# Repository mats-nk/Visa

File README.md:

# "Visa" Introduction

Visa is old norse for "Show" and thats what this project is about.

## First boot:
 - Activate a AP "LED_MATRIX"
 - Configure WiFi and an MQTT broker

## Second boot and thereafter:
 - Publish to MQTT broker what IP it has got
 - Other configuration is acomplished by publish to specific MQTT topics.

# `tools` folder

Here you can find some python tool for get "weather data to MQTT topics" and "MQTT topics to other MQTT topics" with transformation.

### `weather_mqtt.py` — fetches weather from Open-Meteo or wttr.in and publishes to MQTT
 - Multi-language weather descriptions (10 languages)
 - Configurable fields, units, wind direction format
 - In-place countdown between fetches
 - Script version published as MQTT topic

### `mqtt_bridge.py` — forwards MQTT topics with transforms
 - Normal 1-to-1 forwarding
 - Automatic round-robin when multiple sources share the same destination
 - Transform pipeline: round, scale, offset, suffix, prefix, template, json_field
 - Wildcard subscriptions with dynamic destination topics
 - Script version published as MQTT topic

### `setup.sh` — creates the venv, installs dependencies and runs a smoke test

# MQTT Topic Reference

All topics use the pattern `<hostname>/<suffix>`.

Default hostname is `LED_MATRIX`. Replace with your configured hostname throughout.

All values are persisted to EEPROM unless noted otherwise.

---

## Runtime topics

### `LED_MATRIX/value`
Display a message.
- Long messages (wider than display) scroll continuously.
- Short messages (fits on display) are shown statically.
- A queued message waits until the current scroll pass completes before displaying.
- Supports Swedish characters: `å ä ö Å Ä Ö`
- Supports degree symbol: `°` (UTF-8 `0xC2 0xB0`, auto-transcoded to Latin-1 `0xB0`)

```bash
# Plain text
mosquitto_pub -h <MQTT broker> -t "LED_MATRIX/value" -m "Hello World"

# Swedish characters
mosquitto_pub -h <MQTT broker> -t "LED_MATRIX/value" -m "Hej Sverige åäö"

# Temperature with degree symbol
mosquitto_pub -h <MQTT broker> -t "LED_MATRIX/value" -m "Temp: 22°C"
mosquitto_pub -h <MQTT broker> -t "LED_MATRIX/value" -m "Ute: -5°C  Inne: 21°C"

# Time and date (shell substitution)
mosquitto_pub -h <MQTT broker> -t "LED_MATRIX/value" -m "$(date +'%H:%M')"
mosquitto_pub -h <MQTT broker> -t "LED_MATRIX/value" -m "$(date +'%A %d %B')"

# Combined sensor readout
mosquitto_pub -h <MQTT broker> -t "LED_MATRIX/value" -m "$(date +'%H:%M')  Temp: 22°C  Luftfukt: 45%"

# Clear the display
mosquitto_pub -h <MQTT broker> -t "LED_MATRIX/value" -m ""
```

---

### `LED_MATRIX/speed`
Scroll step delay in milliseconds. Lower = faster scroll.

Range: `10` – `500` ms. Default: `100`

```bash
mosquitto_pub -h <MQTT broker> -t "LED_MATRIX/speed" -m "50"    # fast
mosquitto_pub -h <MQTT broker> -t "LED_MATRIX/speed" -m "100"   # default
mosquitto_pub -h <MQTT broker> -t "LED_MATRIX/speed" -m "200"   # slow
```

---

### `LED_MATRIX/intensity`
Display brightness.
Range: `0` (minimum) – `15` (maximum). Default: `5`

```bash
mosquitto_pub -h <MQTT broker> -t "LED_MATRIX/intensity" -m "0"    # minimum (nearly off)
mosquitto_pub -h <MQTT broker> -t "LED_MATRIX/intensity" -m "5"    # default
mosquitto_pub -h <MQTT broker> -t "LED_MATRIX/intensity" -m "15"   # maximum
```

---

### `LED_MATRIX/state`
Turn display on or off.

`1` = on, `0` = off. Not persisted — resets to on after reboot.

When turned back on the previous message resumes automatically.

```bash
mosquitto_pub -h <MQTT broker> -t "LED_MATRIX/state" -m "0"   # off
mosquitto_pub -h <MQTT broker> -t "LED_MATRIX/state" -m "1"   # on
```

---

### `LED_MATRIX/anim`
Animation mode for scrolling messages.

Default: `0`

| Value | Name         | Description                                    |
|-------|------        |-------------                                   |
| `0`   | Scroll left  | Text enters from right, exits left *(default)* |
| `1`   | Scroll right | Text enters from left, exits right             |
| `2`   | Scroll up    | Text shifts upward each tick                   |
| `3`   | Scroll down  | Text shifts downward each tick                 |
| `4`   | Flip LR      | Static left↔right mirror, redrawn each tick    |
| `5`   | Flip UD      | Static top↔bottom mirror, redrawn each tick    |
| `6`   | Rotate CW    | 90° clockwise rotation applied each tick       |
| `7`   | Invert       | All pixels toggled each tick                   |
| `8`   | Bounce       | Ping-pong: scroll left then right alternating  |
| `9`   | Scroll left + invert | Scroll left with inverted pixels       |
| `10`  | Blink        | Whole display blinks at scroll speed           |
| `11`  | Wipe in      | Columns fill inward from both edges            |
| `12`  | Wipe out     | Columns clear outward from centre              |

```bash
mosquitto_pub -h <MQTT broker> -t "LED_MATRIX/anim" -m "0"    # scroll left (default)
mosquitto_pub -h <MQTT broker> -t "LED_MATRIX/anim" -m "1"    # scroll right
mosquitto_pub -h <MQTT broker> -t "LED_MATRIX/anim" -m "8"    # bounce
mosquitto_pub -h <MQTT broker> -t "LED_MATRIX/anim" -m "10"   # blink
```

---

### `LED_MATRIX/pause`
Hold time in milliseconds after each full message pass before restarting.

`0` = no pause (continuous). Max: `30000` ms. Default: `0`

Behaviour differs by message length:
- **Long message (scrolling):** display is blank during the pause.
- **Short message (static):** message stays visible during the pause, then clears briefly before redisplaying.

```bash
mosquitto_pub -h <MQTT broker> -t "LED_MATRIX/pause" -m "0"      # continuous (default)
mosquitto_pub -h <MQTT broker> -t "LED_MATRIX/pause" -m "2000"   # 2 second pause
mosquitto_pub -h <MQTT broker> -t "LED_MATRIX/pause" -m "5000"   # 5 second pause
mosquitto_pub -h <MQTT broker> -t "LED_MATRIX/pause" -m "10000"  # 10 second pause
```

---

### `LED_MATRIX/align`
Text alignment for short messages that fit within the display width.

Has no effect on scrolling messages. Default: `0`

| Value | Alignment |
|-------|-----------|
| `0` | Left *(default)* |
| `1` | Centre |
| `2` | Right |

```bash
mosquitto_pub -h <MQTT broker> -t "LED_MATRIX/align" -m "0"   # left (default)
mosquitto_pub -h <MQTT broker> -t "LED_MATRIX/align" -m "1"   # centre — good for time "12:45"
mosquitto_pub -h <MQTT broker> -t "LED_MATRIX/align" -m "2"   # right
```

---

## Hardware config topics

Changes to hardware config topics trigger a full matrix reinitialisation without reboot.

The display briefly shows `reconfigured!` then resumes the previous message.

### `LED_MATRIX/config/hwtype`
MAX7219 module hardware type.

Default: `3` (FC16)

| Value | Type |
|-------|------|
| `0` | PAROLA_HW |
| `1` | GENERIC_HW |
| `2` | ICSTATION_HW |
| `3` | FC16_HW *(default)* |

```bash
mosquitto_pub -h <MQTT broker> -t "LED_MATRIX/config/hwtype" -m "3"   # FC16 (most common)
mosquitto_pub -h <MQTT broker> -t "LED_MATRIX/config/hwtype" -m "1"   # Generic
```

---

### `LED_MATRIX/config/numdevices`
Number of chained MAX7219 modules.

Range: `1` – `8`. Default: `4`

```bash
mosquitto_pub -h <MQTT broker> -t "LED_MATRIX/config/numdevices" -m "4"   # 4 modules
mosquitto_pub -h <MQTT broker> -t "LED_MATRIX/config/numdevices" -m "8"   # 8 modules
```

---

### `LED_MATRIX/config/clkpin`
GPIO number for SPI CLK.

Default (ESP8266 D1 Mini): `14` (D5)

```bash
mosquitto_pub -h <MQTT broker> -t "LED_MATRIX/config/clkpin" -m "14"
```

---

### `LED_MATRIX/config/datapin`
GPIO number for SPI DATA/MOSI.

Default (ESP8266 D1 Mini): `13` (D7)

```bash
mosquitto_pub -h <MQTT broker> -t "LED_MATRIX/config/datapin" -m "13"
```

---

### `LED_MATRIX/config/cspin`
GPIO number for SPI CS/SS.

Default (ESP8266 D1 Mini): `12` (D6)

```bash
mosquitto_pub -h <MQTT broker> -t "LED_MATRIX/config/cspin" -m "12"
```

---

### `LED_MATRIX/config/auxpin`
GPIO number for auxiliary output (e.g. LDR enable).

Default (ESP8266): `3`

```bash
mosquitto_pub -h <MQTT broker> -t "LED_MATRIX/config/auxpin" -m "3"
```

---

### `LED_MATRIX/config/hbledpin`
GPIO number for heartbeat LED.

Default (ESP8266): `2`

```bash
mosquitto_pub -h <MQTT broker> -t "LED_MATRIX/config/hbledpin" -m "2"
```

---

### `matrix/config/hostname`
Rename the device. **Fixed topic** — always `matrix/config/hostname` regardless of current hostname, so any device can be targeted before its hostname is known.

Max 31 characters. Takes effect immediately — device reconnects to MQTT with the new name.

```bash
mosquitto_pub -h <MQTT broker> -t "matrix/config/hostname" -m "LOBBY"
mosquitto_pub -h <MQTT broker> -t "matrix/config/hostname" -m "RECEPTION"
mosquitto_pub -h <MQTT broker> -t "matrix/config/hostname" -m "LED_MATRIX"   # reset to default
```

---

## Status topic (published by device)

### `LED_MATRIX/config/status`
Published by the device on every MQTT connect and after errors.
Includes firmware version as the first field.

```
fw=2025-03-07.1 hostname=LED_MATRIX mqtt=<MQTT broker>:1883 hwType=3 devices=8 clk=14 data=13 cs=12 aux=3 hbled=2 speed=100 intensity=5 anim=0 pause=0 align=0
```

```bash
# Subscribe to watch status
mosquitto_sub -h <MQTT broker> -t "LED_MATRIX/config/status"

# Trigger a status republish by cycling state
mosquitto_pub -h <MQTT broker> -t "LED_MATRIX/state" -m "1"
```

---

## Active/online topic (published by device)

### `LED_MATRIX/active`
Published as `online` on every MQTT connect. Used by Home Assistant as the availability topic — entities show as unavailable if the device drops off the network.

```bash
mosquitto_sub -h <MQTT broker> -t "LED_MATRIX/active"
```

---

## Practical examples

### Clock display — centred, refreshed every minute
```bash
# Set up display style once
mosquitto_pub -h <MQTT broker> -t "LED_MATRIX/align"   -m "1"     # centre
mosquitto_pub -h <MQTT broker> -t "LED_MATRIX/pause"   -m "0"     # no pause
mosquitto_pub -h <MQTT broker> -t "LED_MATRIX/anim"    -m "0"

# Then update time each minute via cron or Home Assistant automation
mosquitto_pub -h <MQTT broker> -t "LED_MATRIX/value"   -m "$(date +'%H:%M')"
```

### Temperature ticker from Home Assistant
```bash
# Long scrolling message with temperature and humidity
mosquitto_pub -h <MQTT broker> -t "LED_MATRIX/value" -m "Ute: -3°C  Inne: 21°C  Luftfukt: 42%"
mosquitto_pub -h <MQTT broker> -t "LED_MATRIX/speed" -m "80"
mosquitto_pub -h <MQTT broker> -t "LED_MATRIX/pause" -m "3000"
```

### Night mode — dim and slow
```bash
mosquitto_pub -h <MQTT broker> -t "LED_MATRIX/intensity" -m "1"
mosquitto_pub -h <MQTT broker> -t "LED_MATRIX/speed"     -m "150"
```

### Day mode — bright and fast
```bash
mosquitto_pub -h <MQTT broker> -t "LED_MATRIX/intensity" -m "10"
mosquitto_pub -h <MQTT broker> -t "LED_MATRIX/speed"     -m "60"
```

### Turn off at bedtime, on at wake-up
```bash
mosquitto_pub -h <MQTT broker> -t "LED_MATRIX/state" -m "0"   # off — previous message saved
mosquitto_pub -h <MQTT broker> -t "LED_MATRIX/state" -m "1"   # on  — previous message resumes
```

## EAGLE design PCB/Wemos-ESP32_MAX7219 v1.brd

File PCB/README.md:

# MAX7219 4x8x8 matrix module

# ESP8266 

# ESP32

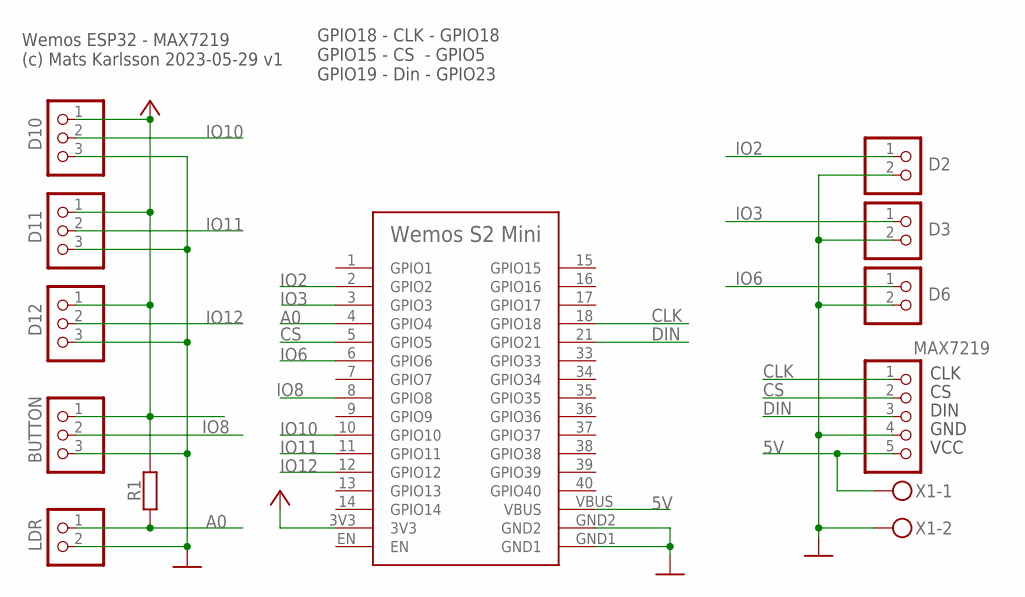
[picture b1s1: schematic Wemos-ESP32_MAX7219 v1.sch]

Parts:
BUTTON: PINHD-1X3; 1X03
D2, D3, D6: PINHD-1X2; 1X02
D10, D11, D12: PINHD-1X3; 1X03
LDR: PINHD-1X2; 1X02
MAX7219: PINHD-1X5; 1X05
R1: R-EU_M0805; M0805
U$1: WEMOS_S2_MINI
X1: W237-102

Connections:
5V: MAX7219.5, U$1.VBUS, X1.1
A0: LDR.1, R1.2, U$1.4 (GPIO4)
CLK: MAX7219.1, U$1.18 (GPIO18)
CS: MAX7219.2, U$1.5 (GPIO5)
DIN: MAX7219.3, U$1.21 (GPIO21)
GND: BUTTON.3, D2.2, D3.2, D6.2, D10.3, D11.3, D12.3, LDR.2, MAX7219.4, U$1.GND1, U$1.GND2, X1.2
IO2: D2.1, U$1.2 (GPIO2)
IO3: D3.1, U$1.3 (GPIO3)
IO6: D6.1, U$1.6 (GPIO6)
IO8: BUTTON.2, U$1.8 (GPIO8)
IO10: D10.2, U$1.10 (GPIO10)
IO11: D11.2, U$1.11 (GPIO11)
IO12: D12.2, U$1.12 (GPIO12)
VCC: BUTTON.1, D10.1, D11.1, D12.1, R1.1, U$1.3V3

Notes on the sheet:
Wemos ESP32 - MAX7219 (c) Mats Karlsson 2023-05-29 v1
GPIO18 - CLK - GPIO18 GPIO15 - CS - GPIO5 GPIO19 - Din - GPIO23
CLK
DIN
GND
VCC

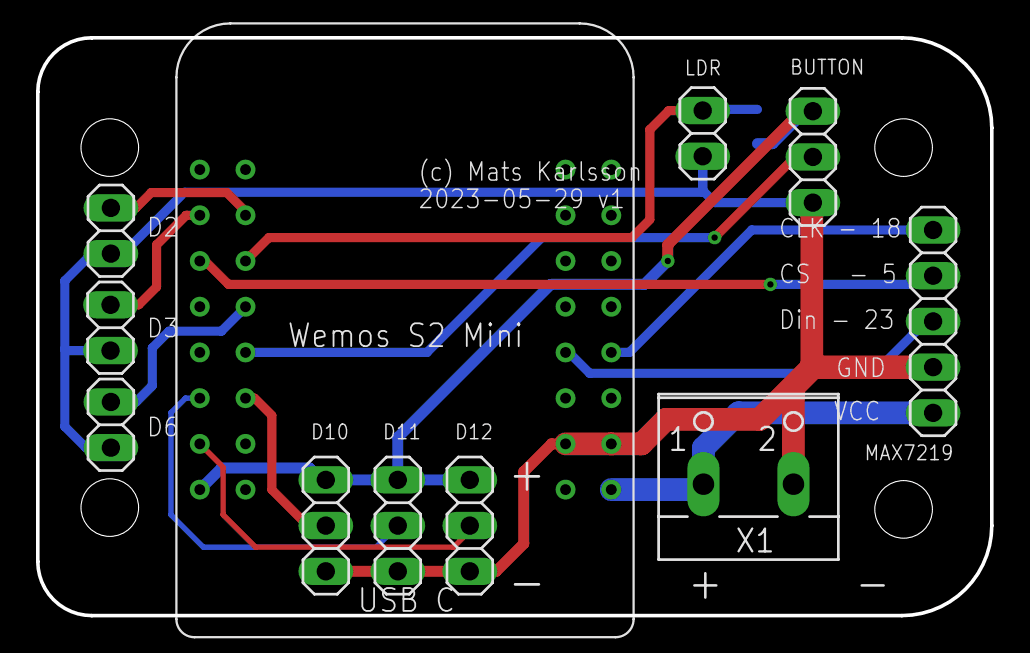
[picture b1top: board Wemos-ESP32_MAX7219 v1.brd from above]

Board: 2 copper layers, 53.0 x 32.1 mm, 12 parts (1 on the bottom side), 14 nets.

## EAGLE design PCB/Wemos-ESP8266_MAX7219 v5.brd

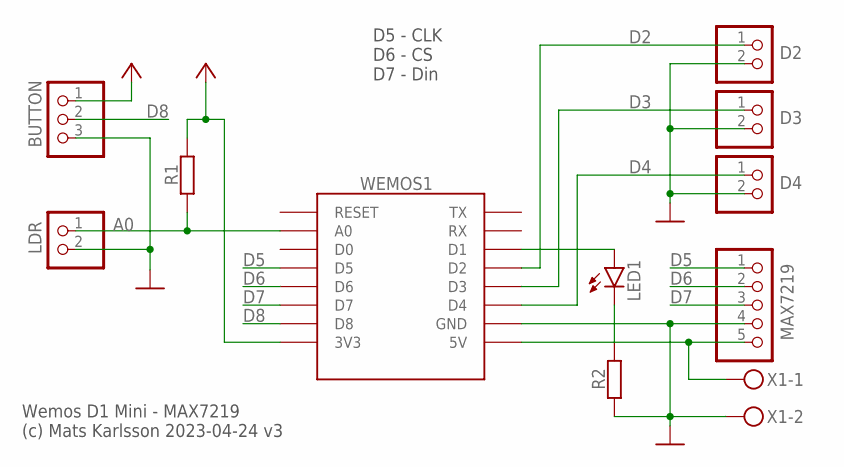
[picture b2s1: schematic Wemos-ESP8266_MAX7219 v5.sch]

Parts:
BUTTON: PINHD-1X3; 1X03
D2, D3, D4: PINHD-1X2; 1X02
LDR: PINHD-1X2; 1X02
LED1: LEDCHIPLED_1206; CHIPLED_1206
MAX7219: PINHD-1X5; 1X05
R1, R2: R-EU_M0805; M0805
WEMOS1: WEMOS-D1-MINI
X1: W237-102

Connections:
5V: MAX7219.5, WEMOS1.5V, X1.1
A0: LDR.1, R1.2, WEMOS1.A0
D2: D2.1, WEMOS1.D2
D3: D3.1, WEMOS1.D3
D4: D4.1, WEMOS1.D4
D5: MAX7219.1, WEMOS1.D5
D6: MAX7219.2, WEMOS1.D6
D7: MAX7219.3, WEMOS1.D7
D8: BUTTON.2, WEMOS1.D8
GND: BUTTON.3, D2.2, D3.2, D4.2, LDR.2, MAX7219.4, R2.2, WEMOS1.GND, X1.2
unnamed: LED1.C, R2.1
unnamed: LED1.A, WEMOS1.D1
VCC: BUTTON.1, R1.1, WEMOS1.3V3

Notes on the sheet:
Wemos D1 Mini - MAX7219 (c) Mats Karlsson 2023-04-24 v3
D5 - CLK D6 - CS D7 - Din

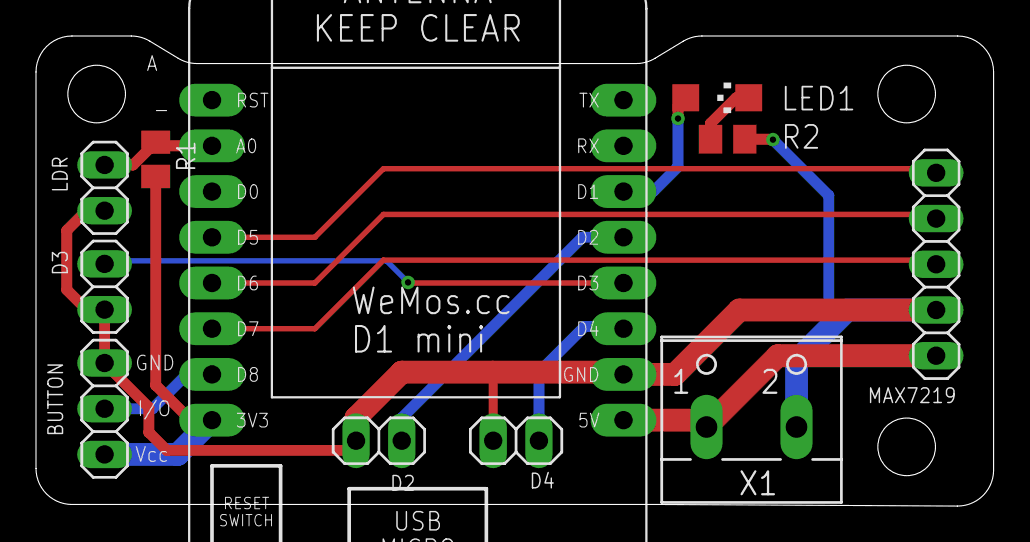
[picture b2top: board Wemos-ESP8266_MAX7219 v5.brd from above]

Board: 2 copper layers, 53.2 x 26.1 mm, 11 parts (0 on the bottom side), 13 nets.

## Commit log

2023-02-16 Update README.md
    First version
2023-02-16 Create ToDo.txt
    First release
2023-02-16 Create Dependencies.txt
    First
2023-02-21 Update README.md
    Added discord channel invite
2023-06-09 PCB for Wemos D1 Mini and Wemos S2 Mini
    PCB for MAX7219 made in Eagle (But I will change to KiCAD due to the changes in Eagle that Autodesk is doing).
2023-06-09 Hardware designs
    Made in Eagle PCB CAD
2023-06-09 Minor corrections
2025-10-13 Create visa.ino
    Initial
2026-03-07 Revise README content for clarity and conciseness
    Removed introductory text and features list from README.
2026-03-07 Enhance README with MQTT and configuration details
    Expanded the README.md to include detailed MQTT topic references, usage examples, and hardware configuration topics for the LED_MATRIX project.
2026-03-07 Document tools folder and Python scripts in README
    Added tools folder section with descriptions for Python scripts.
2026-03-22 Add IP address publishing for OTA updates via MQTT
    Publish the device's IP address for easier OTA targeting.
2026-03-22 Add GitHub Actions workflow for build and release
